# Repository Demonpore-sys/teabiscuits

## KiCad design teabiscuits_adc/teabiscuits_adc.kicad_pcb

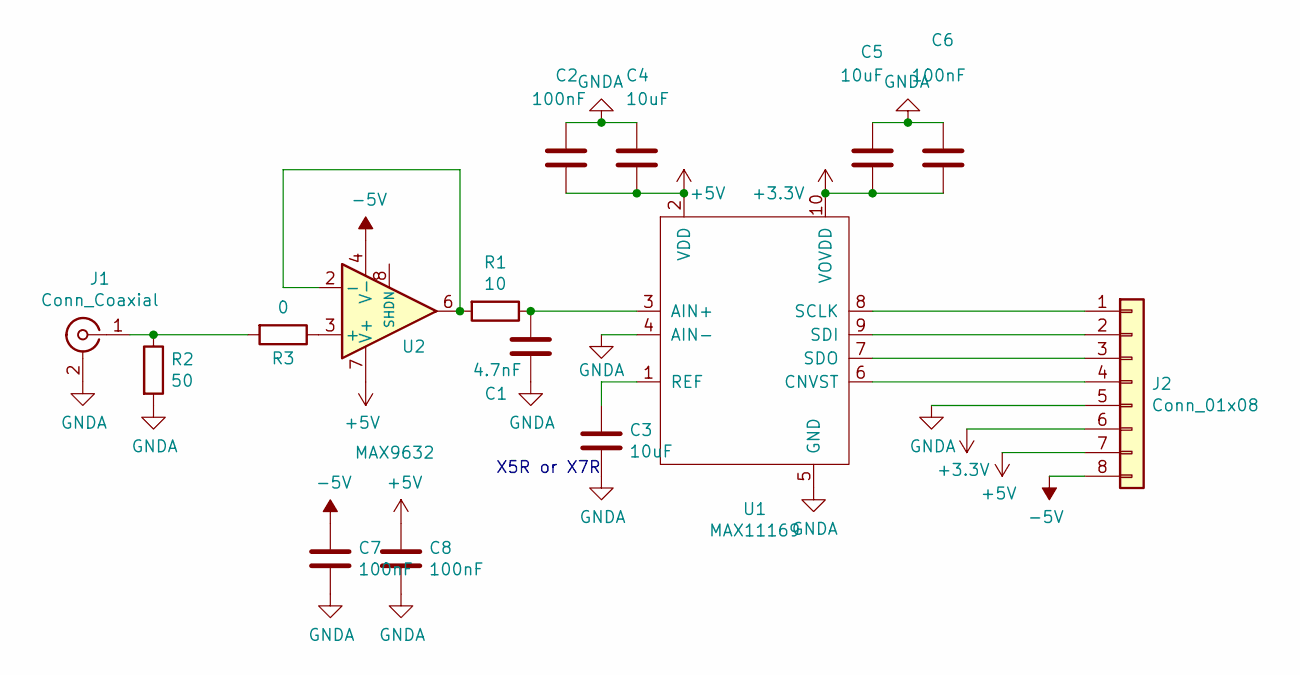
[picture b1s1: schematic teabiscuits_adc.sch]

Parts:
C1: 4.7nF; C_0805_2012Metric
C2, C6, C7, C8: 100nF; C_0805_2012Metric
C3, C4, C5: 10uF; C_0805_2012Metric
J1: Conn_Coaxial; SMA_Amphenol_901-144_Vertical
J2: Conn_01x08; IDC-Header_2x04_P2.54mm_Horizontal
R1: 10; R_0805_2012Metric
R2: 50; R_0805_2012Metric
R3: 0; R_0805_2012Metric
U1: MAX11169; MSOP-10_3x3mm_P0.5mm
U2: MAX9632; SOIC-8_3.9x4.9mm_P1.27mm

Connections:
+3V3: C5.2, C6.2, J2.6, U1.10 (VOVDD)
+5V: C2.2, C4.2, C8.1, J2.7, U1.2 (VDD), U2.7 (V+)
-5V: C7.1, J2.8, U2.4 (V-)
GNDA: C1.2, C2.1, C3.2, C4.1, C5.1, C6.1, C7.2, C8.2, J1.2 (Ext), J2.5, R2.2, U1.4 (AIN-), U1.5 (GND)
unnamed: C1.1, R1.1, U1.3 (AIN+)
unnamed: C3.1, U1.1 (REF)
unnamed: J1.1 (In), R2.1, R3.2
unnamed: J2.1, U1.8 (SCLK)
unnamed: J2.2, U1.9 (SDI)
unnamed: J2.3, U1.7 (SDO)
unnamed: J2.4, U1.6 (CNVST)
unnamed: R1.2, U2.2 (-), U2.6
unnamed: R3.1, U2.3 (+)

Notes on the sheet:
X5R or X7R

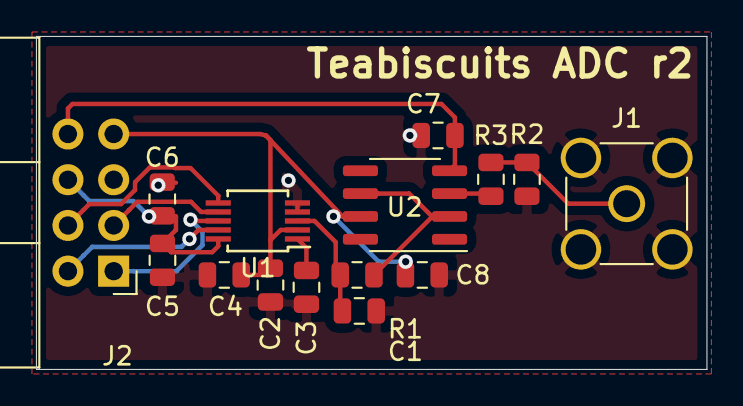
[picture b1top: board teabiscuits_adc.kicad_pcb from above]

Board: 2 copper layers, 37.2 x 18.5 mm, 15 parts (0 on the bottom side), 13 nets.

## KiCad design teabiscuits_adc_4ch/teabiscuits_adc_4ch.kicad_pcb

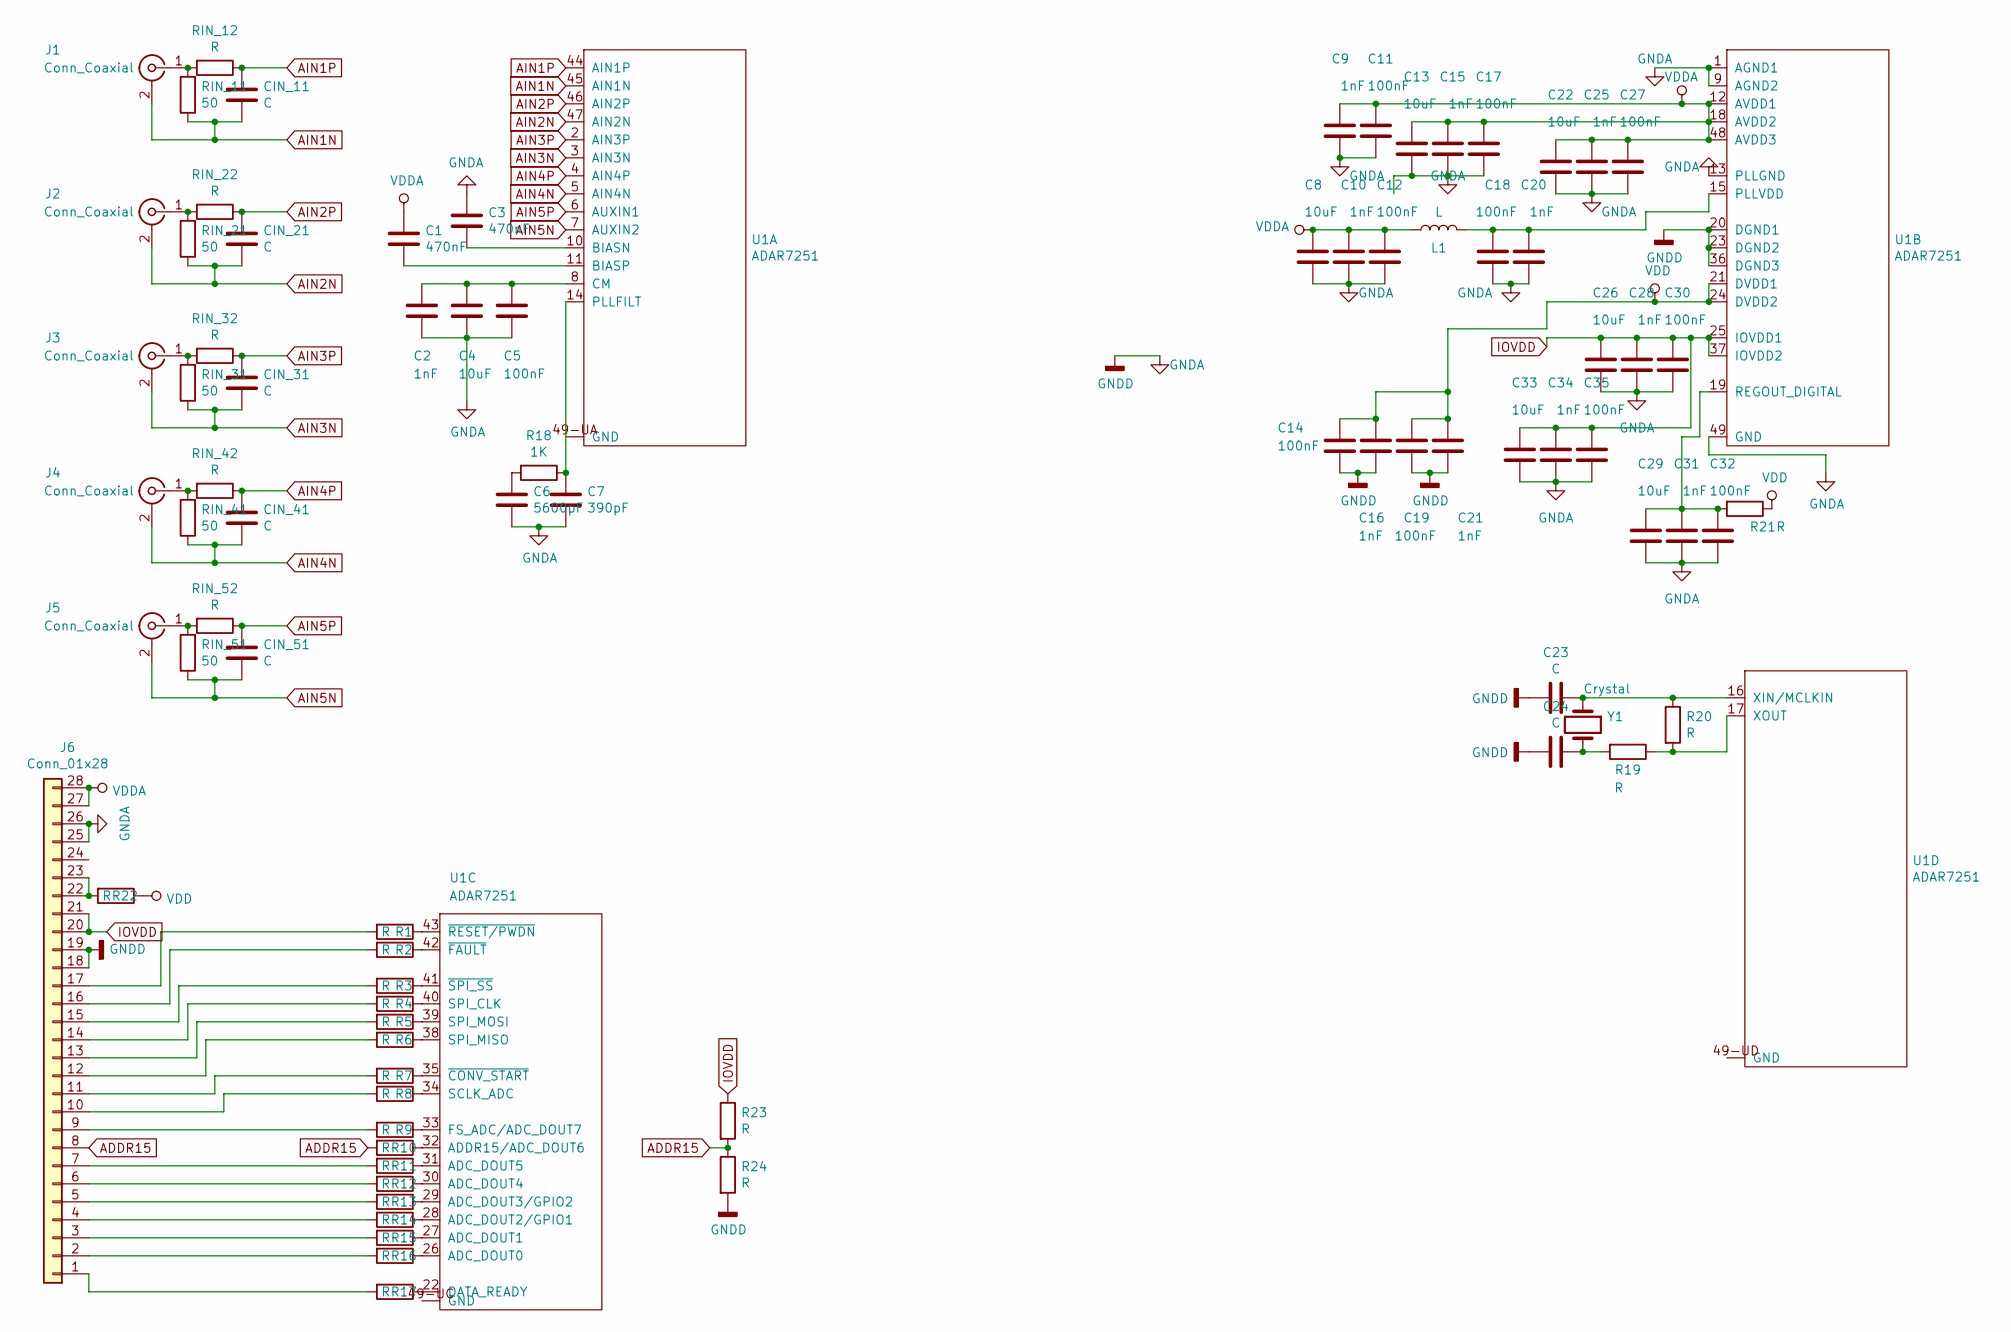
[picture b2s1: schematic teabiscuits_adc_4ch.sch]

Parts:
C1, C3: 470nF; C_0805_2012Metric
C2, C9, C10, C15, C16, C20, C21, C25, C28, C31, C34: 1nF; C_0603_1608Metric
C4, C8, C13, C22, C26, C29, C33: 10uF; C_0805_2012Metric
C5, C11, C12, C14, C17, C18, C19, C27, C30, C32, C35: 100nF; C_0603_1608Metric
C6: 5600pF; C_0603_1608Metric
C7: 390pF; C_0603_1608Metric
C23, C24: C; C_0603_1608Metric
CIN_11, CIN_21, CIN_31, CIN_41, CIN_51: C; C_0805_2012Metric
J1, J2, J3, J4, J5: Conn_Coaxial; MMCX_Molex_73415-0961_Horizontal_1.0mm-PCB
J6: Conn_01x28; PinHeader_2x14_P2.54mm_Vertical
L1: L; L_1210_3225Metric
R1, R2, R3, R4, R5, R6, R7, R8, R9, R10, R11, R12, R13, R14, R15, R16, R17, R19, R20, R21, R22, R23, R24: R; R_0805_2012Metric
R18: 1K; R_0603_1608Metric
RIN_11, RIN_21, RIN_31, RIN_41, RIN_51: 50; R_0805_2012Metric
RIN_12, RIN_22, RIN_32, RIN_42, RIN_52: R; R_0805_2012Metric
U1: ADAR7251; LFCSP-48-1EP_7x7mm_P0.5mm_EP4.1x4.1mm_ThermalVias
Y1: Crystal; Crystal_SMD_3225-4Pin_3.2x2.5mm

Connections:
ADDR15: J6.8, R10.2, R23.2, R24.1
AIN1N: CIN_11.1, J1.2 (Ext), RIN_11.1, U1.45 (AIN1N)
AIN1P: CIN_11.2, RIN_12.1, U1.44 (AIN1P)
AIN2N: CIN_21.1, J2.2 (Ext), RIN_21.1, U1.47 (AIN2N)
AIN2P: CIN_21.2, RIN_22.1, U1.46 (AIN2P)
AIN3N: CIN_31.1, J3.2 (Ext), RIN_31.1, U1.3 (AIN3N)
AIN3P: CIN_31.2, RIN_32.1, U1.2 (AIN3P)
AIN4N: CIN_41.1, J4.2 (Ext), RIN_41.1, U1.5 (AIN4N)
AIN4P: CIN_41.2, RIN_42.1, U1.4 (AIN4P)
AIN5N: CIN_51.1, J5.2 (Ext), RIN_51.1, U1.7 (AUXIN2)
AIN5P: CIN_51.2, RIN_52.1, U1.6 (AUXIN1)
GNDA: C2.2, C3.1, C4.2, C5.2, C6.2, C7.2, C8.2, C9.2, C10.2, C11.2, C12.2, C13.2, C14.2, C15.2, C16.2, C17.2, C18.2, C19.2, C20.2, C21.2, C22.2, C23.2, C24.2, C25.2, C26.2, C27.2, C28.2, C29.2, C30.2, C31.2, C32.2, C33.2, C34.2, C35.2, J6.18, J6.19, J6.25, J6.26, R24.2, U1.1 (AGND1), U1.9 (AGND2), U1.13 (PLLGND), U1.20 (DGND1), U1.23 (DGND2), U1.36 (DGND3), U1.49 (GND)
IOVDD: C26.1, C28.1, C30.1, C33.1, C34.1, C35.1, J6.20, J6.21, R23.1, U1.25 (IOVDD1), U1.37 (IOVDD2)
unnamed: C1.2, U1.11 (BIASP)
unnamed: C2.1, C4.1, C5.1, U1.8 (CM)
unnamed: C3.2, U1.10 (BIASN)
unnamed: C6.1, R18.2
unnamed: C7.1, R18.1, U1.14 (PLLFILT)
unnamed: C18.1, C20.1, L1.2, U1.15 (PLLVDD)
unnamed: C23.1, R20.1, U1.16 (XIN/MCLKIN), Y1.1
unnamed: C24.1, R19.2, Y1.2
unnamed: C29.1, C31.1, C32.1, R21.2, U1.19 (REGOUT_DIGITAL)
unnamed: J1.1 (In), RIN_11.2, RIN_12.2
unnamed: J2.1 (In), RIN_21.2, RIN_22.2
unnamed: J3.1 (In), RIN_31.2, RIN_32.2
unnamed: J4.1 (In), RIN_41.2, RIN_42.2
unnamed: J5.1 (In), RIN_51.2, RIN_52.2
unnamed: J6.1, R17.2
unnamed: J6.2, R16.2
unnamed: J6.3, R15.2
unnamed: J6.4, R14.2
unnamed: J6.5, R13.2
unnamed: J6.6, R12.2
unnamed: J6.7, R11.2
unnamed: J6.9, R9.2
unnamed: J6.10, R8.2
unnamed: J6.11, R7.2
unnamed: J6.12, R6.2
unnamed: J6.13, R5.2
unnamed: J6.14, R4.2
unnamed: J6.15, R3.2
unnamed: J6.16, R2.2
unnamed: J6.17, R1.2
unnamed: J6.22, J6.23, R22.2
unnamed: R1.1, U1.43 (~RESET/PWDN)
unnamed: R2.1, U1.42 (~FAULT)
unnamed: R3.1, U1.41 (~SPI_SS)
unnamed: R4.1, U1.40 (SPI_CLK)
unnamed: R5.1, U1.39 (SPI_MOSI)
unnamed: R6.1, U1.38 (SPI_MISO)
unnamed: R7.1, U1.35 (~CONV_START)
unnamed: R8.1, U1.34 (SCLK_ADC)
unnamed: R9.1, U1.33 (FS_ADC/ADC_DOUT7)
unnamed: R10.1, U1.32 (ADDR15/ADC_DOUT6)
unnamed: R11.1, U1.31 (ADC_DOUT5)
unnamed: R12.1, U1.30 (ADC_DOUT4)
unnamed: R13.1, U1.29 (ADC_DOUT3/GPIO2)
unnamed: R14.1, U1.28 (ADC_DOUT2/GPIO1)
unnamed: R15.1, U1.27 (ADC_DOUT1)
unnamed: R16.1, U1.26 (ADC_DOUT0)
unnamed: R17.1, U1.22 (DATA_READY)
unnamed: R19.1, R20.2, U1.17 (XOUT)
VDD: C14.1, C16.1, C19.1, C21.1, R21.1, R22.1, U1.21 (DVDD1), U1.24 (DVDD2)
VDDA: C1.1, C8.1, C9.1, C10.1, C11.1, C12.1, C13.1, C15.1, C17.1, C22.1, C25.1, C27.1, J6.27, J6.28, L1.1, U1.12 (AVDD1), U1.18 (AVDD2), U1.48 (AVDD3)

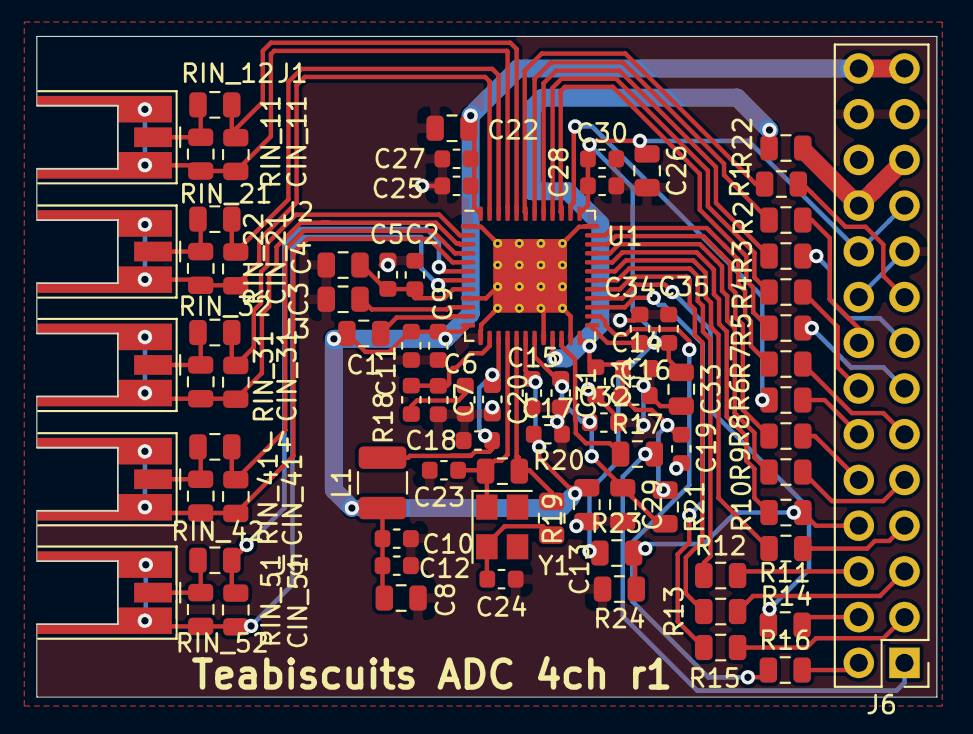
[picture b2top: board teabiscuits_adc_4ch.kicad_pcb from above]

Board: 2 copper layers, 50.0 x 36.7 mm, 83 parts (0 on the bottom side), 64 nets.

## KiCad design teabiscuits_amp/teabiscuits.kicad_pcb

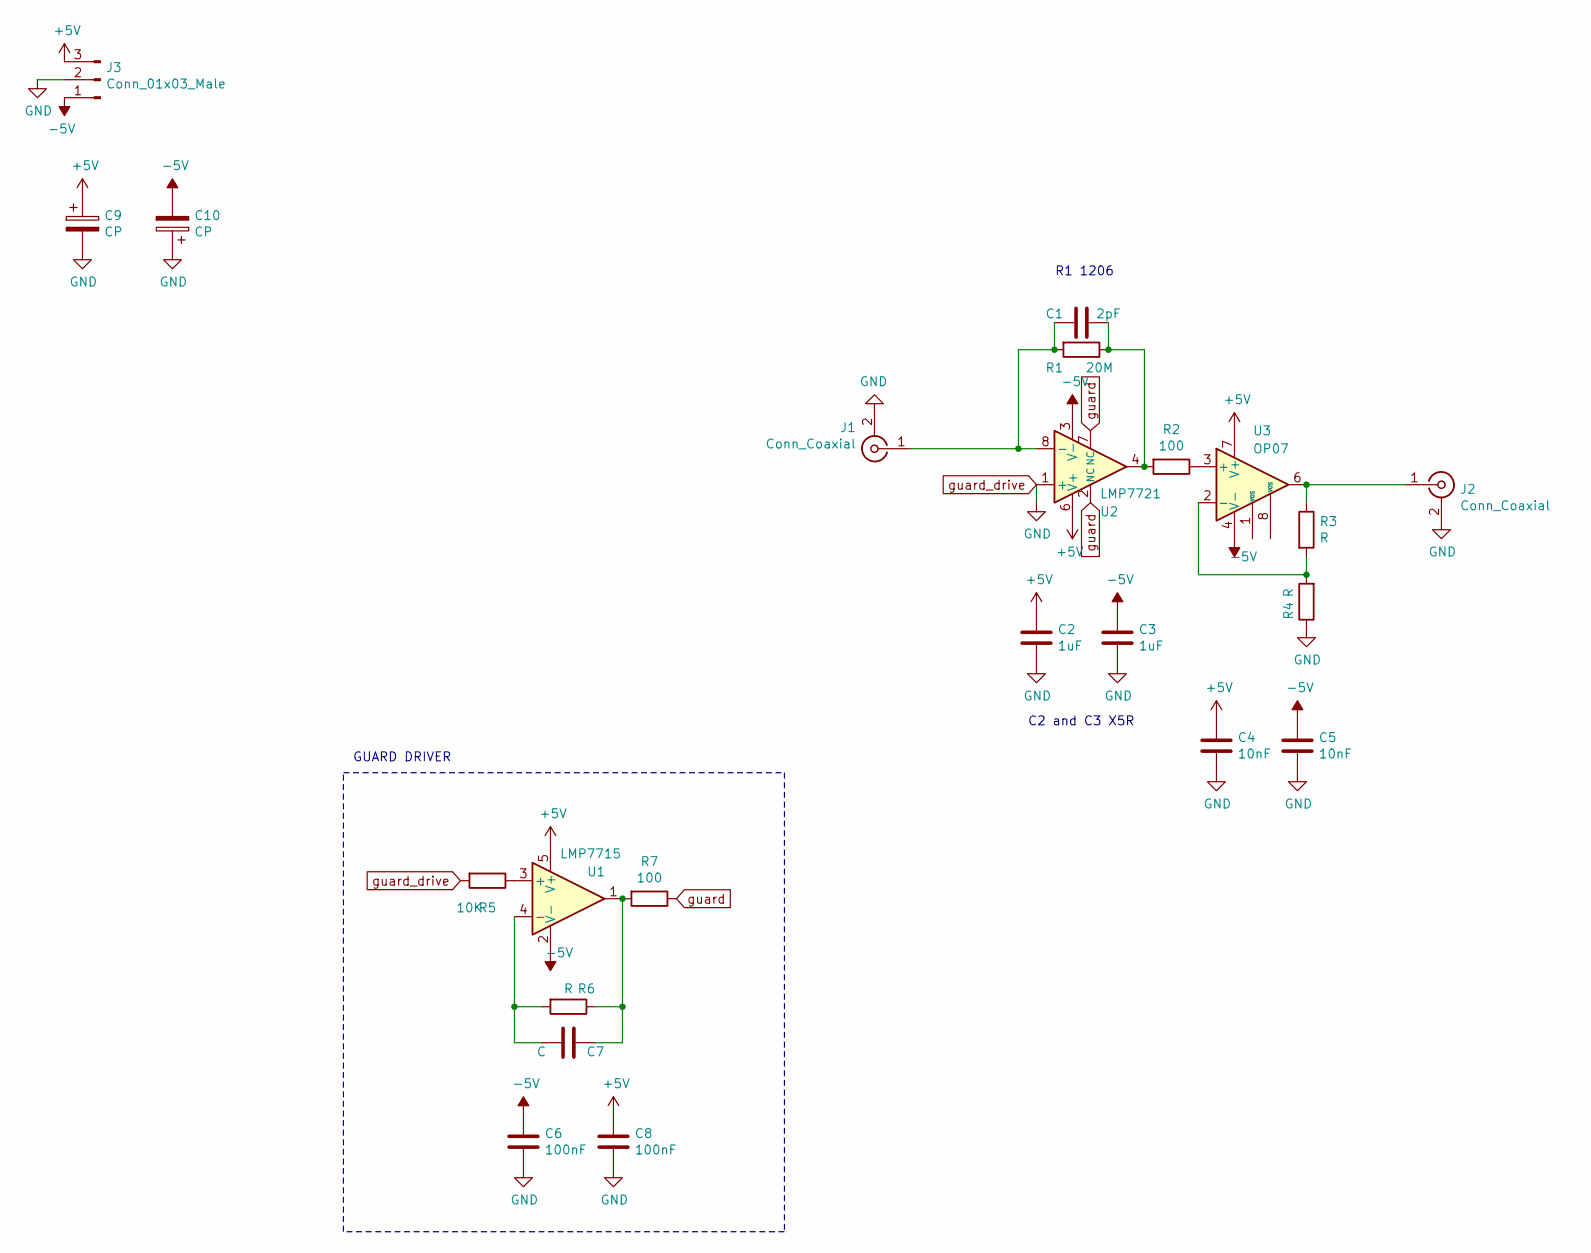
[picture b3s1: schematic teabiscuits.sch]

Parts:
C1: 2pF; C_0805_2012Metric
C2, C3: 1uF; C_0805_2012Metric
C4, C5: 10nF; C_0805_2012Metric
C6, C8: 100nF; C_0805_2012Metric
C7: C; C_0805_2012Metric
C9, C10: CP; CP_EIA-6032-15_Kemet-U
J1, J2: Conn_Coaxial; MMCX_Molex_73415-0961_Horizontal_1.0mm-PCB
J3: Conn_01x03_Male; PinSocket_1x03_P2.54mm_Horizontal
R1: 20M; R_1206_3216Metric
R2: 100; R_0805_2012Metric
R3, R4, R6: R; R_0805_2012Metric
R5: 10K; R_0805_2012Metric
R7: 100; R_1206_3216Metric
U1: LMP7715; SOT-23-5
U2: LMP7721; SOIC-8_3.9x4.9mm_P1.27mm
U3: OP07; SOIC-8_3.9x4.9mm_P1.27mm

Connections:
+5V: C2.1, C4.1, C8.1, C9.1, J3.3, U1.5 (V+), U2.6 (V+), U3.7 (V+)
-5V: C3.1, C5.1, C6.1, C10.2, J3.1, U1.2 (V-), U2.3 (V-), U3.4 (V-)
unnamed: C1.1, R1.1, R2.2, U2.4
unnamed: C1.2, J1.1 (In), R1.2, U2.8 (-)
unnamed: C7.1, R6.1, R7.2, U1.1
unnamed: C7.2, R6.2, U1.4 (-)
unnamed: J2.1 (In), R3.1, U3.6
unnamed: R2.1, U3.3 (+)
unnamed: R3.2, R4.2, U3.2 (-)
unnamed: R5.1, U1.3 (+)
guard: R7.1, U2.2 (NC), U2.7 (NC)
guard_drive: C2.2, C3.2, C4.2, C5.2, C6.2, C8.2, C9.2, C10.1, J1.2 (Ext), J2.2 (Ext), J3.2, R4.1, R5.2, U2.1 (+)

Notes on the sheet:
C2 and C3 X5R
R1 1206
GUARD DRIVER

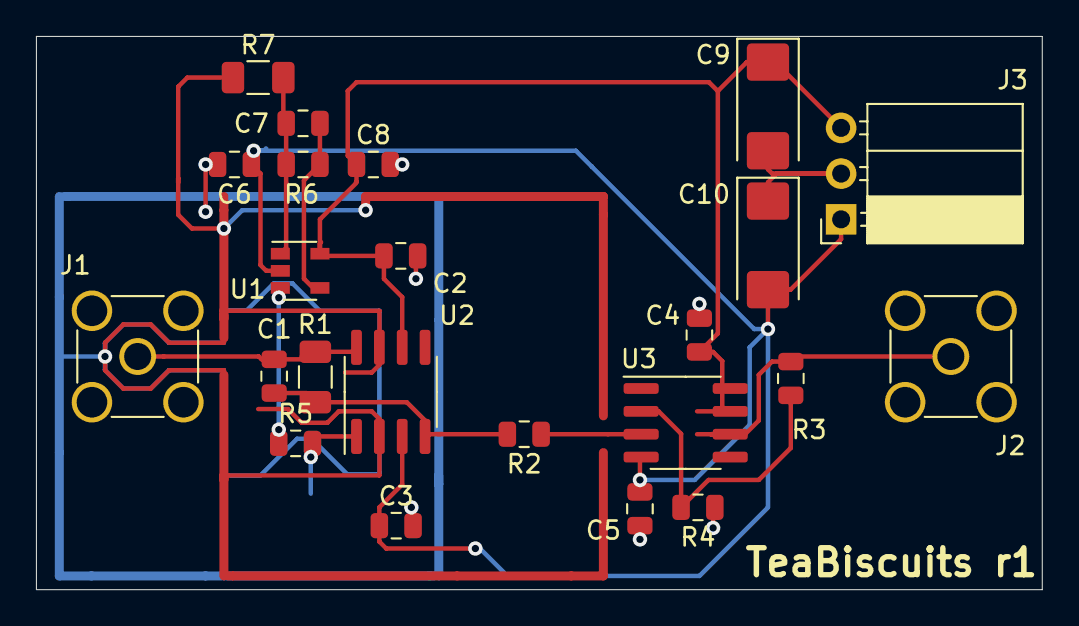
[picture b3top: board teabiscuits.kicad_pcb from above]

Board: 2 copper layers, 55.9 x 30.7 mm, 23 parts (0 on the bottom side), 12 nets.

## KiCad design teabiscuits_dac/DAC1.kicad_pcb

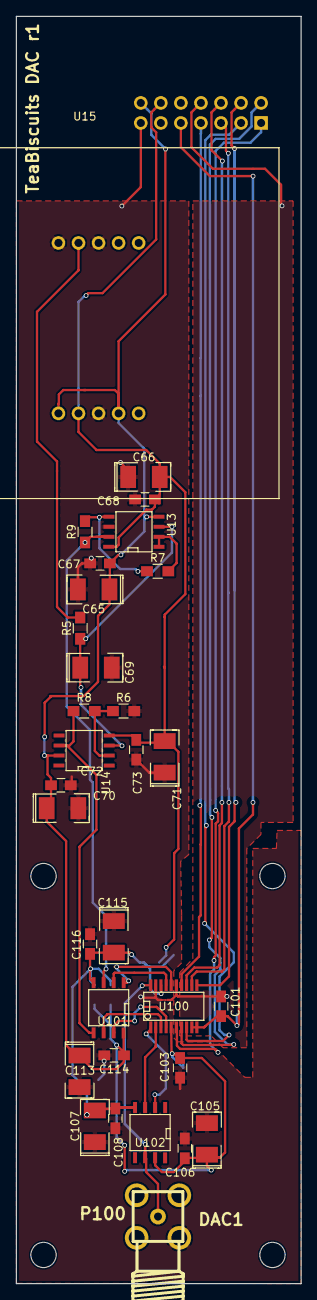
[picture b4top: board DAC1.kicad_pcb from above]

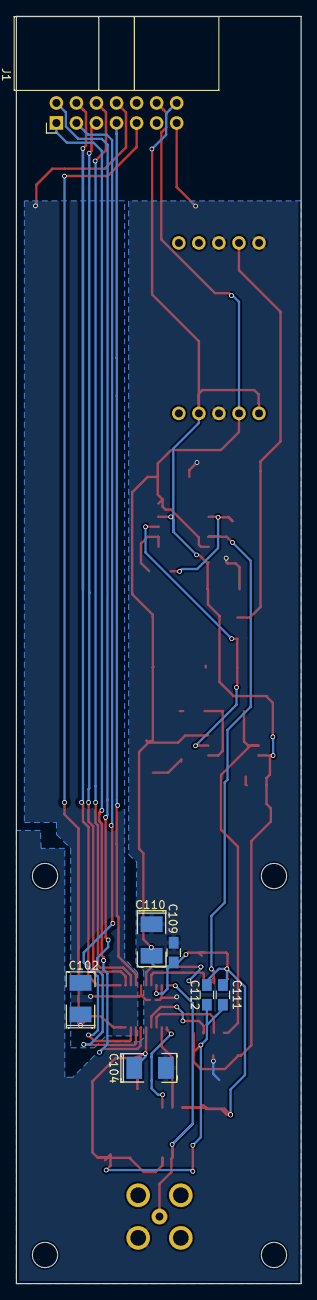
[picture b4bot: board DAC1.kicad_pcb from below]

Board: 2 copper layers, 36.1 x 160.5 mm, 39 parts (7 on the bottom side), 26 nets.

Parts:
C65, C66, C69, C70, C71, C102, C104, C105, C107, C110, C113, C115: 10uF; SMD-1210_Pol
C67, C68, C72, C73, C101, C103, C106, C108, C109, C111, C112, C114, C116: 0.1uF; C_0805_HandSoldering
J1: Conn_01x14; IDC-Header_2x07_P2.54mm_Horizontal
P100: BNC; SMA
R5: 1.5k; R_0805_HandSoldering
R6: 2k5; R_0805_HandSoldering
R7: 10K; R_0805_HandSoldering
R8: 1K; R_0805_HandSoldering
R9: 14K; R_0805_HandSoldering
R100: 0; 0Ohm
U13, U101: AD8676; SOIC-8
U14, U102: AD8675; SOIC-8
U15: A9_REFERENCE; A9REFERENCE
U100: AD5791; SSOP-20

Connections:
7VREF: R5.2, U15.A3
+5V: C101.2, C102.1, J1.9, U100.9, U100.10
+10VREF: R8.1, U14.6, U101.5
+14V: C65.1, C67.1, C70.1, C72.1, C103.2, C104.1, C105.1, C106.1, C111.1, C112.1, C113.1, C114.1, J1.14, U13.4, U14.7, U15.B2, U15.B5, U100.5, U101.8, U102.7
-10VREF: R9.1, U13.7, U101.3
-14V: C66.2, C68.1, C71.2, C73.1, C107.2, C108.1, C109.2, C110.2, C111.2, C112.2, C115.2, C116.1, J1.12, U13.8, U14.4, U15.B4, U100.18, U101.4, U102.4
CLR1: J1.2, U100.7
GNDA: C65.2, C66.1, C67.2, C68.2, C69.2, C70.2, C71.1, C72.2, C73.2, C103.1, C104.2, C105.2, C106.2, C107.1, C108.2, C109.1, C110.1, C113.2, C114.2, C115.1, C116.2, J1.13, P100.2, R6.2, R100.2, U13.6, U15.A2, U15.A4, U15.B3, U100.19
GNDD: C101.1, C102.2, J1.8, R100.1, U100.15
LDAC1: J1.3, U100.8
unnamed: C69.1, R5.1, U13.3, U14.3
unnamed: P100.1, U100.20, U102.6
unnamed: R6.1, R8.2, U14.2
unnamed: R7.1, R9.2, U13.5
unnamed: R7.2, U13.1, U13.2
unnamed: U100.1, U102.2
unnamed: U100.2, U102.3
unnamed: U100.3, U101.6
unnamed: U100.4, U101.7
unnamed: U100.16, U101.1
unnamed: U100.17, U101.2
RESET1: J1.1, U100.6
SCLK: J1.6, U100.13
SDIN: J1.5, U100.12
SDO: J1.4, U100.11
SYNC1: J1.7, U100.14
